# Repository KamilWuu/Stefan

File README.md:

# Stefan

### minisumo robot
### test gita czy cos
## git na windowsie
vscode

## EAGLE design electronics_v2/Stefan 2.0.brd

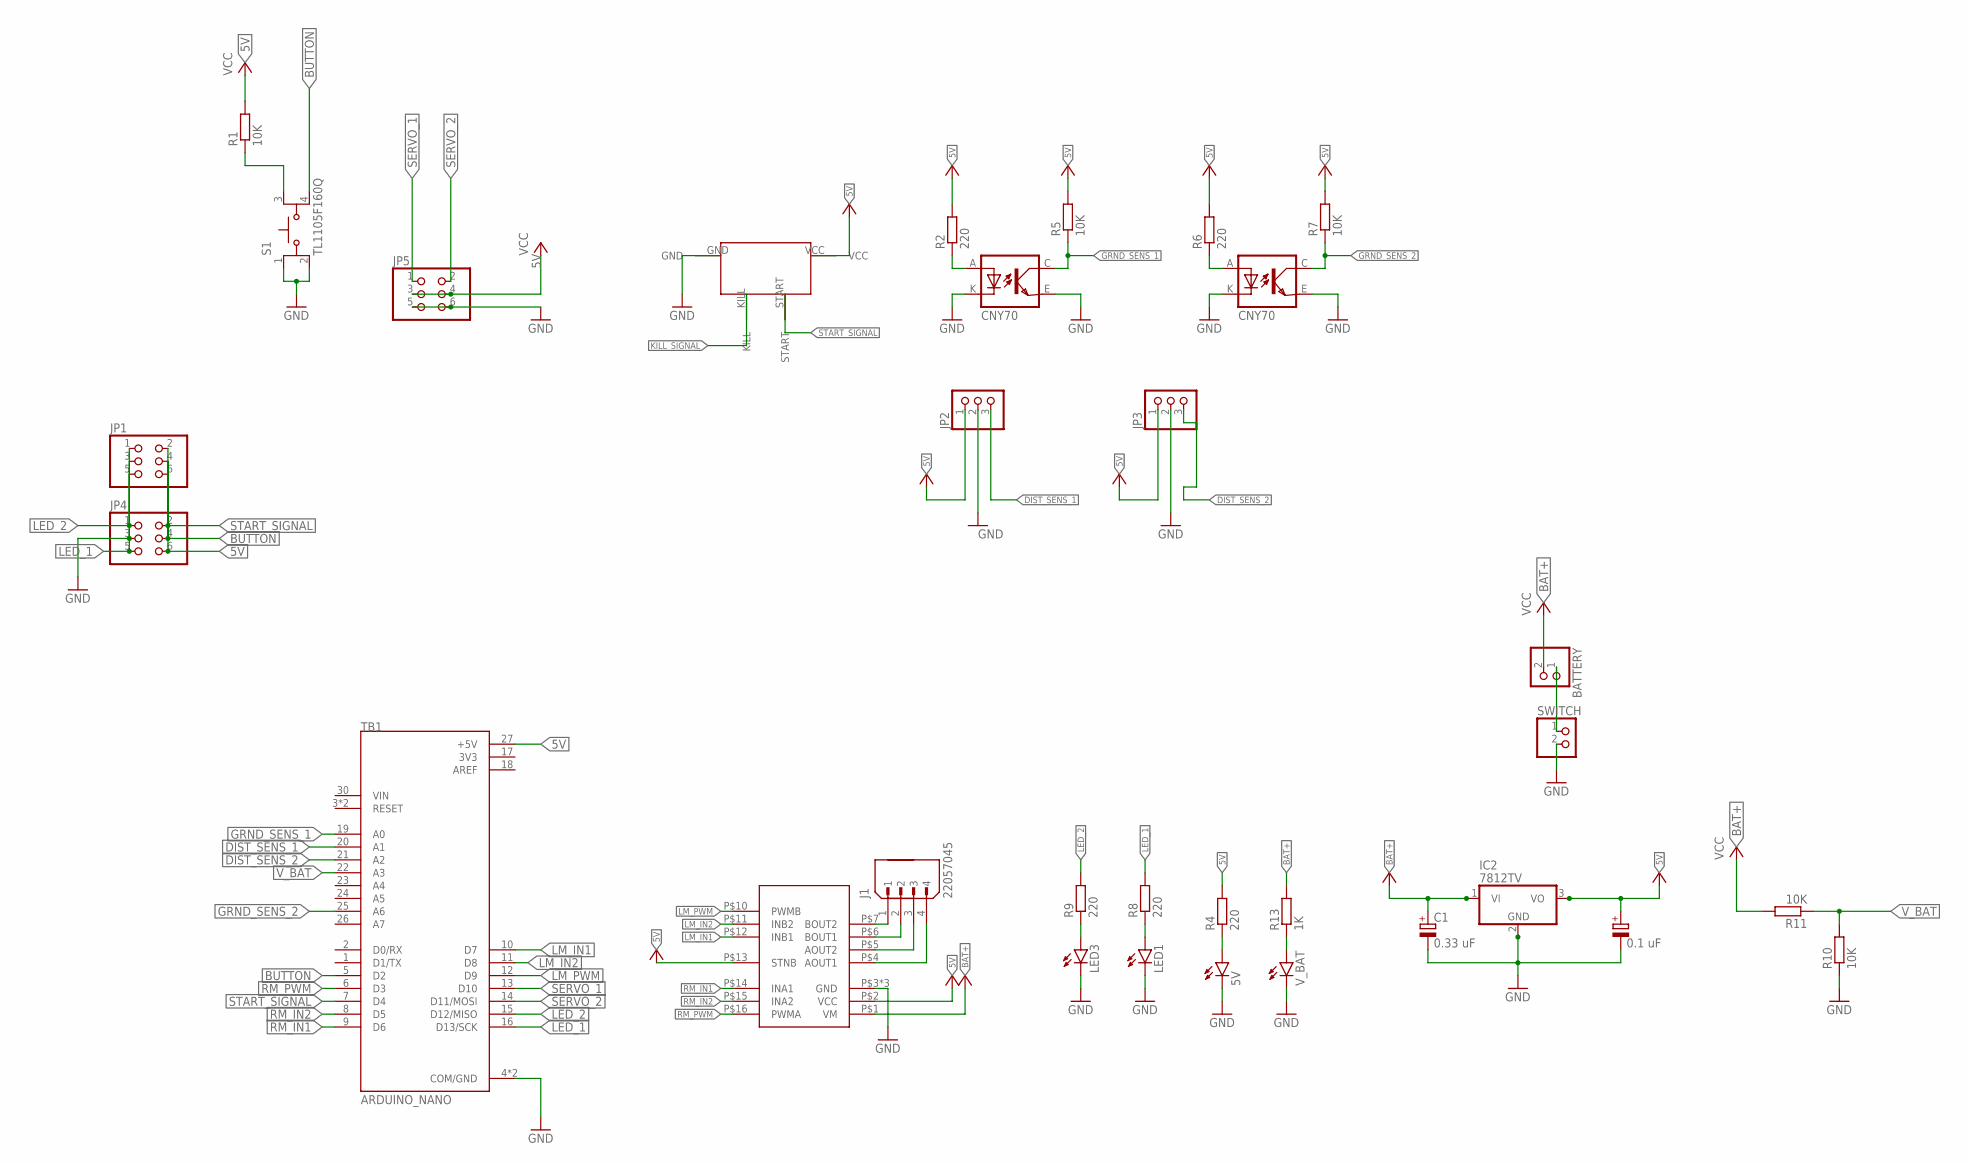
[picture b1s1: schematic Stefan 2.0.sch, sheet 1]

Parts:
5V: LED5MM
BATTERY: PINHD-1X2; 1X02
C1: 0.33 uF; TAP5-70
C2: 0.1 uF; SANYO-OSCON_A
IC2: 7812TV; TO220V
J1: 22057045; MOLEX_22057045
JP1, JP4, JP5: PINHD-2X3; 2X03
JP2, JP3: PINHD-1X3; 1X03
LED1, LED3: LED5MM
R1, R5, R7, R10, R11: 10K; R0805
R2, R4, R6, R8, R9: 220; R0805
R13: 1K; R0805
S1: TL1105F160Q; SW_TL1105F160Q
SUMO_START_MODULE1: SUMO_START_MODULE
SWITCH: PINHD-1X2; 1X02
TB1: ARDUINO_NANO; SHIELD_ARDUINO_NANO
TB2: TB6612MODULE
U$2, U$4: CNY70; 4
V_BAT: LEDCHIPLED_1206; CHIPLED_1206

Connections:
3V3: TB1.17 (3V3)
5V: C2.+, IC2.3 (VO), JP1.6, JP2.1, JP3.1, JP4.6, JP5.3, JP5.4, R1.2, R2.2, R4.2, R5.2, R6.2, R7.2, SUMO_START_MODULE1.VCC, TB1.27 (+5V), TB2.P$2 (VCC), TB2.P$13 (STNB)
AREF: TB1.18 (AREF)
BAT+: BATTERY.2, C1.+, IC2.1 (VI), R11.2, R13.2, TB2.P$1 (VM)
BUTTON: JP1.4, JP4.4, S1.4, TB1.5 (D2)
DIST_SENS_1: JP2.3, TB1.20 (A1)
DIST_SENS_2: JP3.3, TB1.21 (A2)
GND: 5V.K (C), C1.-, C2.-, IC2.2 (GND), JP1.3, JP2.2, JP3.2, JP4.3, JP5.5, JP5.6, LED1.K (C), LED3.K (C), R10.1, S1.1, S1.2, SUMO_START_MODULE1.GND, SWITCH.2, TB1.4 (COM/GND), TB1.29 (COM/GND), TB2.P$3 (GND), TB2.P$8 (GND), TB2.P$9 (GND), U$2.E (EMI), U$2.K (C), U$4.E (EMI), U$4.K (C), V_BAT.C
GRND_SENS_1: R5.1, TB1.19 (A0), U$2.C (COL)
GRND_SENS_2: R7.1, TB1.25 (A6), U$4.C (COL)
KILL_SIGNAL: SUMO_START_MODULE1.KILL
LED_1: JP1.5, JP4.5, R8.2, TB1.16 (D13/SCK)
LED_2: JP1.1, JP4.1, R9.2, TB1.15 (D12/MISO)
LM_IN1: TB1.10 (D7), TB2.P$12 (INB1)
LM_IN2: TB1.11 (D8), TB2.P$11 (INB2)
LM_OUT1: J1.2, TB2.P$6 (BOUT1)
LM_OUT2: J1.1, TB2.P$7 (BOUT2)
LM_PWM: TB1.12 (D9), TB2.P$10 (PWMB)
unnamed: BATTERY.1, SWITCH.1
unnamed: LED3.A, R9.1
unnamed: R2.1, U$2.A
unnamed: R6.1, U$4.A
unnamed: LED1.A, R8.1
unnamed: 5V.A, R4.1
unnamed: R13.1, V_BAT.A
unnamed: R1.1, S1.3
RM_IN1: TB1.9 (D6), TB2.P$14 (INA1)
RM_IN2: TB1.8 (D5), TB2.P$15 (INA2)
RM_OUT1: J1.4, TB2.P$4 (AOUT1)
RM_OUT2: J1.3, TB2.P$5 (AOUT2)
RM_PWM: TB1.6 (D3), TB2.P$16 (PWMA)
SERVO_1: JP5.1, TB1.13 (D10)
SERVO_2: JP5.2, TB1.14 (D11/MOSI)
START_SIGNAL: JP1.2, JP4.2, SUMO_START_MODULE1.START, TB1.7 (D4)
V_BAT: R10.2, R11.1, TB1.22 (A3)

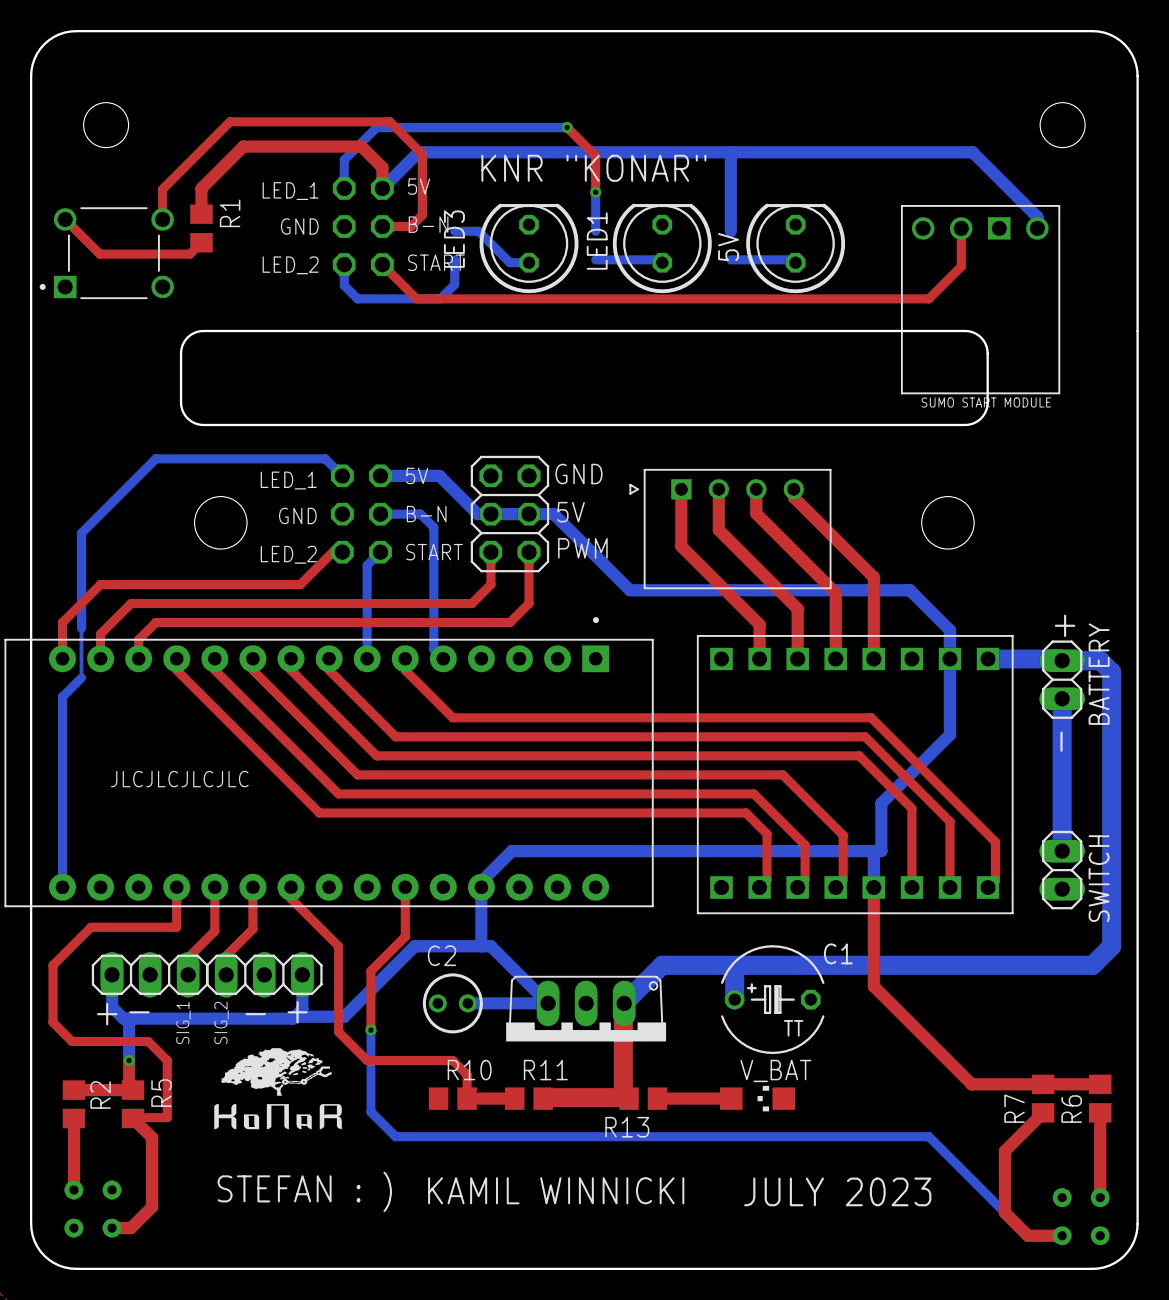
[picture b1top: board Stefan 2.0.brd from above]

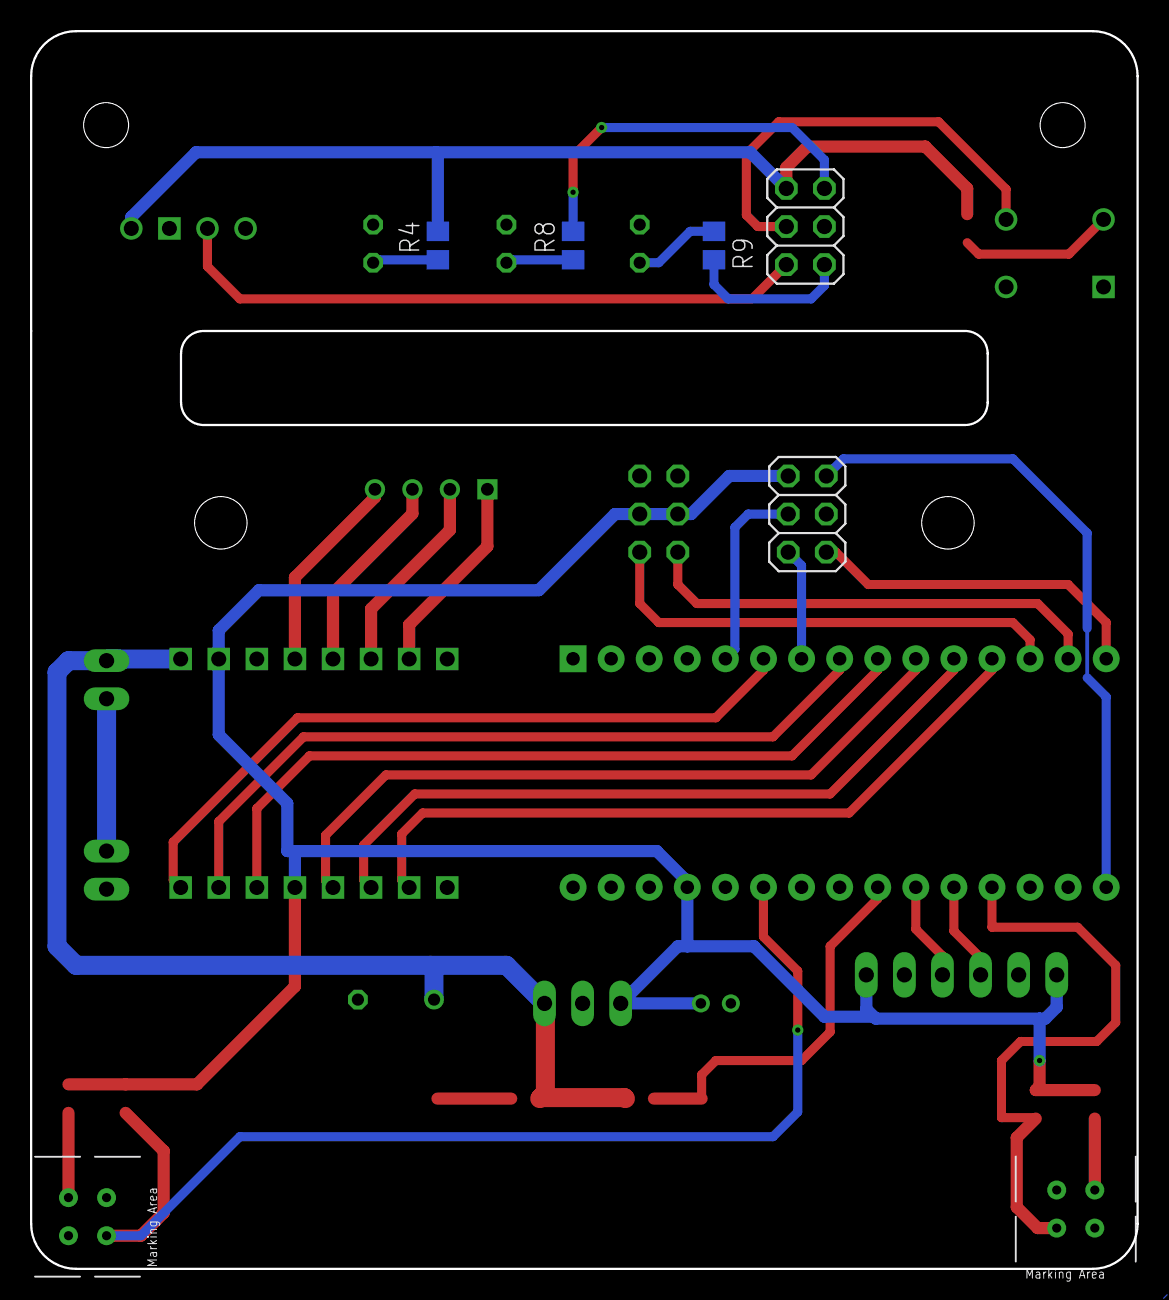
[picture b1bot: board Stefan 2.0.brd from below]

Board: 2 copper layers, 73.8 x 82.6 mm, 32 parts (7 on the bottom side), 32 nets.

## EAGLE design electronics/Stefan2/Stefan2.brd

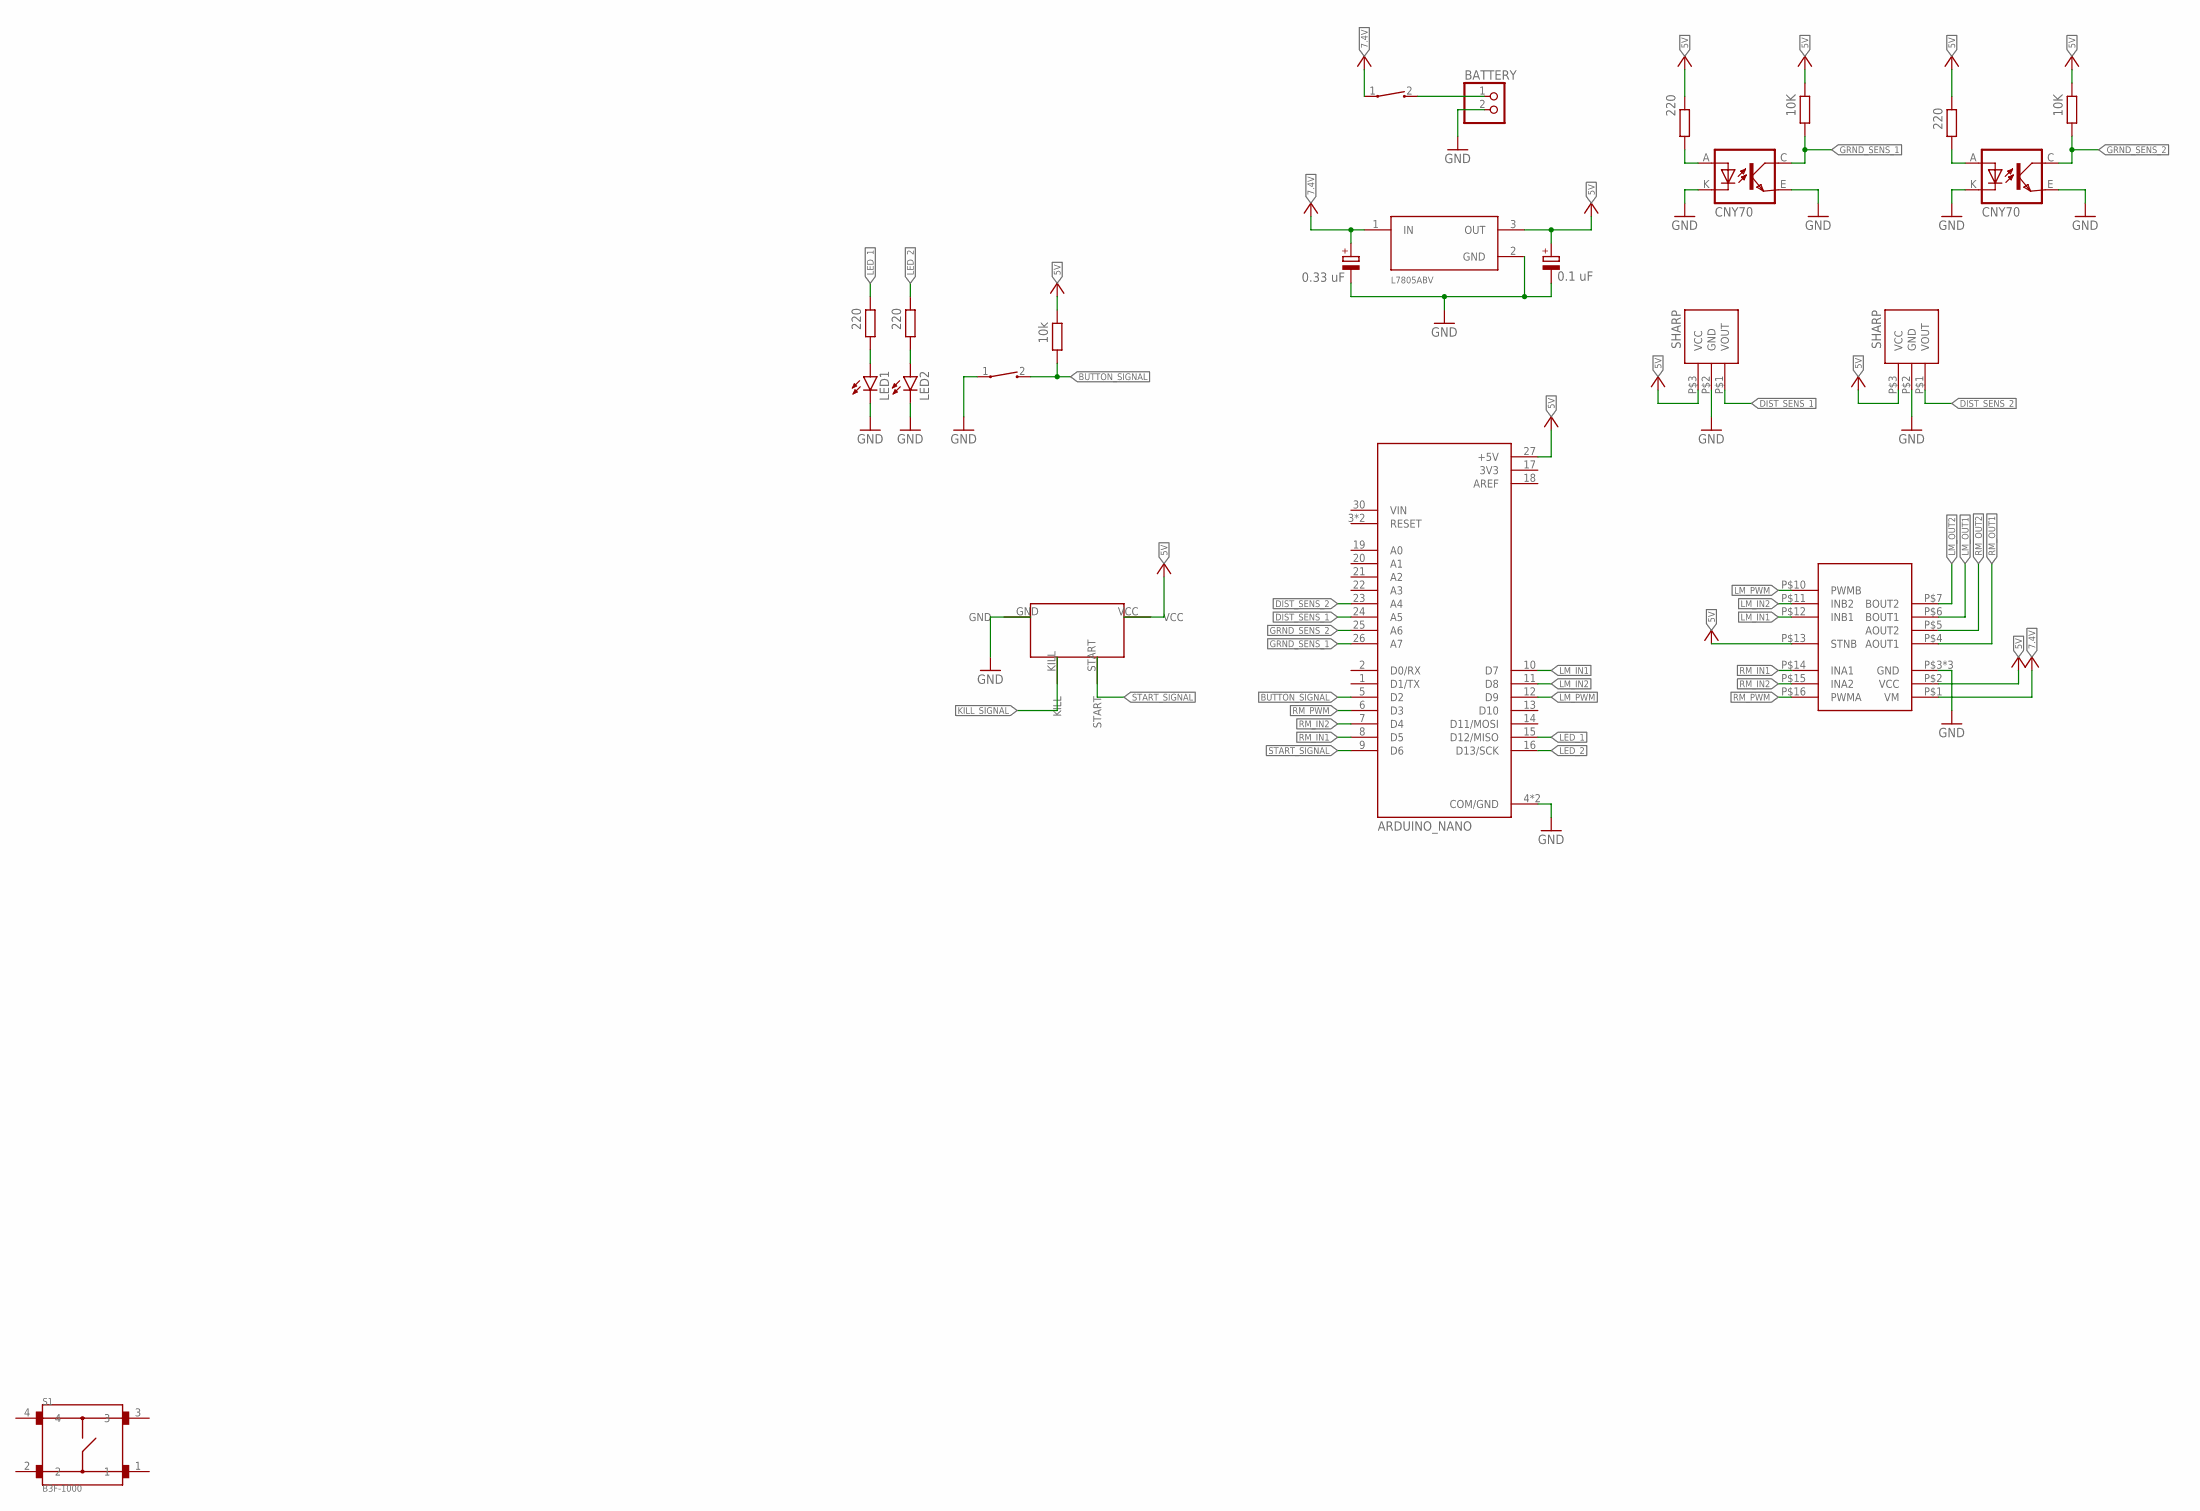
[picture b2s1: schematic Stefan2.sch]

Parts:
BATTERY: PINHD-1X2; 1X02
C1: 0.33 uF; SANYO-OSCON_A
C2: 0.1 uF; SANYO-OSCON_A
LED1, LED2: LED5MM
R1, R4, R6, R7: 220; 0207/10
R3, R8: 10K; 0207/10
R5: 10k; 0207/10
S1: B3F-1000; SW_B3F-1000
SUMO_START_MODULE: SUMO_START_MODULE
SW1, SW2: 147873-1; SW_147873-1
TB1: ARDUINO_NANO; SHIELD_ARDUINO_NANO
TB6612: TB6612MODULE
U1, U3: SHARP; GP2DXX
U2: L7805ABV; TO254P460X1020X1945-3P
U$1, U$3: CNY70; 4

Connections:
3V3: TB1.17 (3V3)
5V: C2.+, R1.2, R3.2, R5.2, R7.2, R8.2, SUMO_START_MODULE.VCC, TB1.27 (+5V), TB6612.P$2 (VCC), TB6612.P$13 (STNB), U1.P$3 (VCC), U2.3 (OUT), U3.P$3 (VCC)
7.4V: C1.+, SW2.1, TB6612.P$1 (VM), U2.1 (IN)
AREF: TB1.18 (AREF)
BUTTON_SIGNAL: R5.1, SW1.2, TB1.5 (D2)
DIST_SENS_1: TB1.24 (A5), U1.P$1 (VOUT)
DIST_SENS_2: TB1.23 (A4), U3.P$1 (VOUT)
GND: BATTERY.2, C1.-, C2.-, LED1.K (C), LED2.K (C), SUMO_START_MODULE.GND, SW1.1, TB1.4 (COM/GND), TB1.29 (COM/GND), TB6612.P$3 (GND), TB6612.P$8 (GND), TB6612.P$9 (GND), U2.2 (GND), U$1.E (EMI), U$1.K (C), U$3.E (EMI), U$3.K (C)
GRND_SENS_1: R3.1, TB1.26 (A7), U$3.C (COL)
GRND_SENS_2: R8.1, TB1.25 (A6), U$1.C (COL)
KILL_SIGNAL: SUMO_START_MODULE.KILL
LED_1: R4.2, TB1.15 (D12/MISO)
LED_2: R6.2, TB1.16 (D13/SCK)
LM_IN1: TB1.10 (D7), TB6612.P$12 (INB1)
LM_IN2: TB1.11 (D8), TB6612.P$11 (INB2)
LM_OUT1: TB6612.P$6 (BOUT1)
LM_OUT2: TB6612.P$7 (BOUT2)
LM_PWM: TB1.12 (D9), TB6612.P$10 (PWMB)
unnamed: LED1.A, R4.1
unnamed: LED2.A, R6.1
unnamed: R1.1, U$3.A
unnamed: R7.1, U$1.A
unnamed: BATTERY.1, SW2.2
unnamed: U1.P$2 (GND), U3.P$2 (GND)
RM_IN1: TB1.8 (D5), TB6612.P$14 (INA1)
RM_IN2: TB1.7 (D4), TB6612.P$15 (INA2)
RM_OUT1: TB6612.P$4 (AOUT1)
RM_OUT2: TB6612.P$5 (AOUT2)
RM_PWM: TB1.6 (D3), TB6612.P$16 (PWMA)
START_SIGNAL: SUMO_START_MODULE.START, TB1.9 (D6)

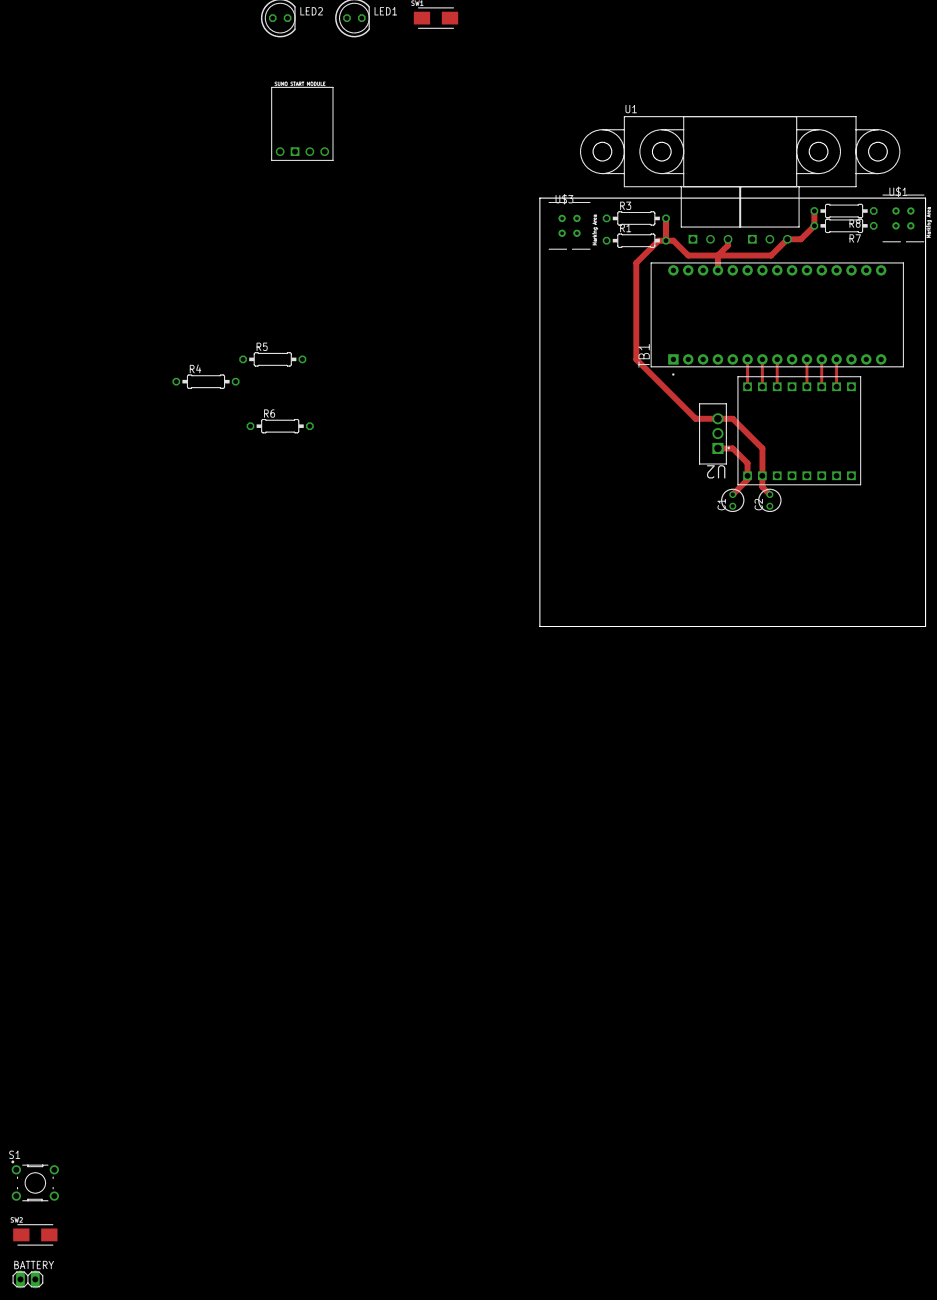
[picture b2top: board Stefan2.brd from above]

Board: 2 copper layers, 66.0 x 73.3 mm, 23 parts (0 on the bottom side), 23 nets.

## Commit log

2022-11-07 opis update
2022-11-07 dodano test gita
2022-11-07 opis comita
2022-11-07 commit cos
2022-11-07 dodano stary kod
2022-11-07 Podzielono kod na czesci nr1
2022-11-07 Podzielono kod na czesci 2
2022-11-07 dodano schemat elektroniki
2022-11-26 dodano wachlarze
2023-02-24 uaktualniony kod oraz nowy pcb0.1
2023-02-24 Dodano dokumentacje
2023-05-13 kopia zapasowa przed zawodami we francji
2023-07-09 zrobiono nowa mechanike i pcb
2024-05-01 mocno rpzedawniona aktualizacja repozytorium
